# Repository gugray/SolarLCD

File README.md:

# LCD Solar Creatures

This repository has all the code and design files for the low-power LCD Solar Creatures
[documented on Hackaday](https://hackaday.io/project/185825-lcd-solar-creatures).

The Solar Creatures are based on a simple 7-segment LCD display and an ATtiny85 microcontroller. They store their energy in a pair of 1.5F supercapacitors that can power them through the night.

When the sun shines, the display plays lively animations: a tiny version of Conway's Game of Life, or randomized rhythmic patterns. As the light fades, the animations slow down, and at night the creatures use their high-power red LED instead to beam out a rhythm. The Creatures draw 11.4μA, 7.3μA and 6.2μA in these modes, respectively.

The Solar Creatures are infused with patterns through and through. The animations and the flashes are all randomly parameterized Euclidean rhythms. You will rarely see the same show twice!

They recognize the periodic peaks and lows of energy, and they keep track of their own age in days. They faithfully report this to you in between two animations, and they also tell you how long they were awake in the last few days.

## Electronics

I designed the schematic and PCB of the creatures in KiCad 5.1.9. The circuitry of the two forms is identical, but because the PCB is different, there are two separate projects. You can find them under [/electronics/v6](electronics/v6) (for larger the Window Squatter) and under [/electronics/vB1](electronics/vB1) (for the smaller Desktop Crawler). The ZIP files with gerber in their name are the exports that I submitted to the PCB fab.

## Laser-cut frame

The frame of both creatures is laser-cut from 3mm acryclic. The vector files for this are in [/design](design). The .ai files are the originals, but I included a version re-saved as Inkscape .svg as well.

## Source code

The source code is straightforward C++ with no bells or whistles. You can find it in [/code/board](code/board). I developed in using the [PlatformIO extension](https://platformio.org/install/ide?install=vscode) for Visual Studio Code, so if you want to explore the code and build it yourself, that might be the easiest way to get started.

The code uses the Arduino framework, but beyond that it has no dependencies and includes no libraries. That's partly because there are no peripherals apart from the  LCD display's HT1621 chip, and partly because any cruft had to be trimmed off to fit into the ATtiny's 8KB flash memory. The HT1621 driver is based on existing precursors (credited at the top of the source files), but it had to be largely reworked to match the weird display I got from AliExpress.

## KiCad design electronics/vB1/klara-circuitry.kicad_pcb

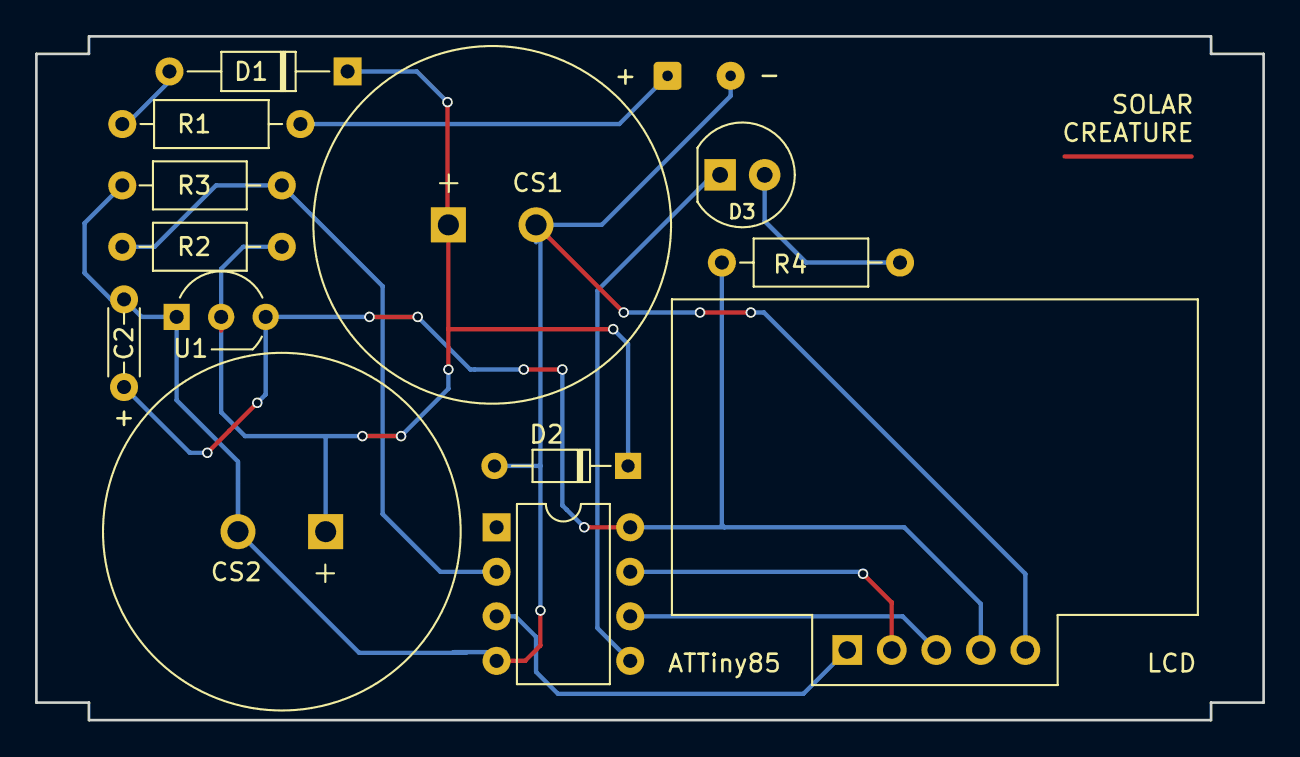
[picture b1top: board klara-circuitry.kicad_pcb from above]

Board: 2 copper layers, 70.0 x 39.0 mm, 14 parts (0 on the bottom side), 11 nets.

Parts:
C2: 1uF; C_Rect_L7.0mm_W2.0mm_P5.00mm
CS1, CS2: 1.5F; CP_Radial_D20.0mm_P5.00mm
D1: 1N60; D_DO-35_SOD27_P10.16mm_Horizontal
D2: Zener; D_DO-34_SOD68_P7.62mm_Horizontal
D3: LED; LED_D5.0mm
LCD: HT1621; LCD_SPI
R1: 59; R_Axial_DIN0207_L6.3mm_D2.5mm_P10.16mm_Horizontal
R2: 1M; R_Axial_DIN0207_L6.3mm_D2.5mm_P10.16mm_Horizontal
R3: 100k; R_Axial_DIN0207_L6.3mm_D2.5mm_P10.16mm_Horizontal
R4: 330; R_Axial_DIN0207_L6.3mm_D2.5mm_P10.16mm_Horizontal
SC1: Solar_Cell; SolderWire-0.1sqmm_1x02_P3.6mm_D0.4mm_OD1mm
U1: MCP1700-3302E; TO-92_Inline_Wide
U3: ATtiny85; DIP-8_W7.62mm

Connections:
unnamed: C2.1, LCD.4, R4.1, U1.3, U3.8
unnamed: C2.2, CS1.2, CS2.2, D2.2, LCD.5, R3.2, SC1.2, U1.1, U3.4
unnamed: CS1.1, CS2.1, D1.1, D2.1, R2.1, U1.2
unnamed: D1.2, R1.2
unnamed: D3.1, U3.5
unnamed: D3.2, R4.2
unnamed: LCD.1, U3.3
unnamed: LCD.2, U3.7
unnamed: LCD.3, U3.6
unnamed: R1.1, SC1.1
unnamed: R2.2, R3.1, U3.2

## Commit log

2022-06-06 initial commit (refactoring from PoC)
2022-06-06 voltage observer logic WIP
2022-06-10 ATtiny/Nano dual platforms; smaller HT1621 buffer; loop mode functions
2022-06-15 voltage-dependent behavior experimentation
2022-06-18 working on power saving
2022-06-18 audio spectrogram simulator
2022-06-19 fix: low-voltage (blinker) mode didn't turn off LCD
2022-06-19 schematic and design (WIP)
2022-06-19 evolution of schematic v1-v2-v3
2022-06-29 dynamic on-screen animations; count msecs for uptime
2022-06-29 code for external voltage observer via nano
2022-07-02 advanced animations: game of life; 2 x euclidean rhythms
2022-07-03 new LED wiring; animation fixes
2022-07-03 more robust (and efficient) VSS measurement
2022-07-03 temperature measured & shown
2022-07-04 temp measurement in voltage board
2022-07-05 design & schematic wip
2022-07-05 time measurement experiments
2022-07-05 final (?) schematic
2022-07-08 reducing code size
2022-07-08 current day and past day uptimes
2022-07-09 fixes: current day and past day uptimes
2022-07-09 removed temperature
2022-07-09 history: auto store 0s in first-use EEPOM
2022-07-16 PCB WIP
2022-07-17 fix: history had uncalibrated (lower) awake time
2022-07-17 for the record: earlier board voltage measurement data
2022-07-17 design/pcb finalized for manufacturing
2022-07-29 fix: detecting new day if MCU doesn't power off in a short night
2022-08-13 fixes to penta frame pcb; alternative small pcb
2022-08-31 PCB update
2022-08-31 rhythmic LED blinkie
2022-09-04 tweak: blink unless voltage clearly growing
2022-09-04 circuit d'oh: measure supercap voltage, not regulator output
2023-02-23 time correction for small creature (none needed)
2023-02-23 stand of small creature
2023-02-23 fix (maybe): no blinking on some nights
2023-03-14 added Inkscape SVG conversion of frame design files
2023-03-14 remove superceded electroncs and design versions
2023-03-14 remove superceded code experiments
2023-03-14 add creature photos
2023-03-14 resize photos
2023-03-15 rename gerber files; video thumbnal
2023-03-15 Create LICENSE
